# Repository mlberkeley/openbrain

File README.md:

# OpenBrain [[PDF Status](https://www.sharelatex.com/github/repos/mlberkeley/openbrain/builds/latest/badge.svg)](https://www.sharelatex.com/github/repos/mlberkeley/openbrain/builds/latest/output.pdf)
The openBrain project for massive asynchronous neurocomputation. 
Read our [white paper here](https://www.sharelatex.com/github/repos/mlberkeley/openbrain/builds/latest/output.pdf).

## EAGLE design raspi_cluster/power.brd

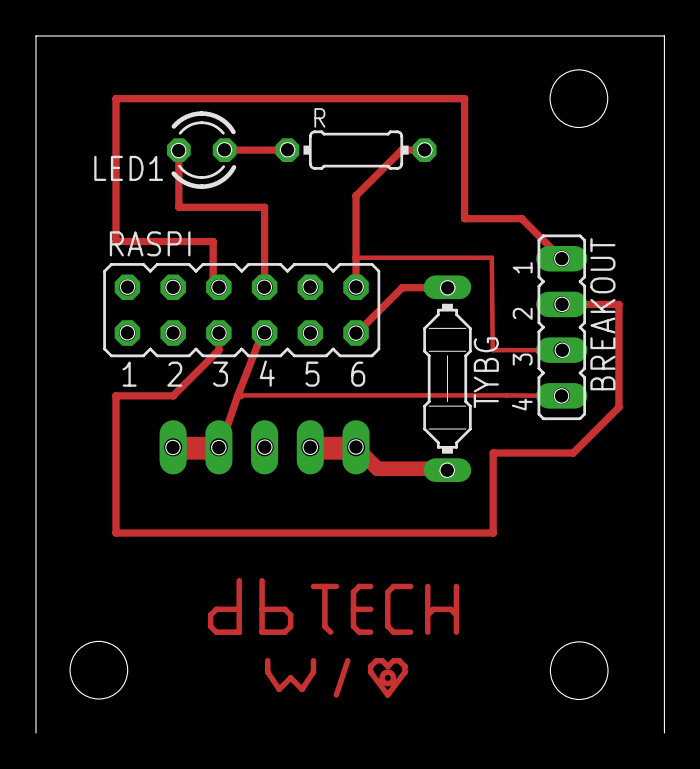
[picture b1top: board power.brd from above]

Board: 2 copper layers, 34.9 x 38.7 mm, 6 parts (1 on the bottom side), 8 nets.

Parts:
5V: 22-23-2051
BREAKOUT: JP4
LED1: TLLR4400; LED3MM
R: 0204/7
RASPI: JP6Q
TYBG: FUSEPICOFUSE; PICOFUSE

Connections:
unnamed: 5V.1, 5V.2, TYBG.2
unnamed: BREAKOUT.3, R.2, RASPI.12
unnamed: LED1.A, R.1
unnamed: BREAKOUT.1, RASPI.6
unnamed: RASPI.11, TYBG.1
unnamed: 5V.4, 5V.5, BREAKOUT.4, RASPI.7
unnamed: BREAKOUT.2, RASPI.5
unnamed: LED1.K, RASPI.8

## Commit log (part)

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2015-12-22 Added a synapto_genesis paper to the research catalogue.
2015-12-22 Added the dentate synaptogenesis paper.
2016-01-03 Working on research proposal.
2016-01-04 Worked on the proposal for plans.
2016-01-04 More work on the proposal
2016-01-04 Working on budget
2016-01-04 Additional work on budget formatting,.
2016-01-04 Finishing budget.
2016-01-04 Finished background
2016-01-04 Misssed something
2016-01-11 Added raspberry pi cluster docs to the repo
2016-01-13 Added schematic and board prototyping for the printed power board
2016-01-13 Proposal finished.
2016-01-13 Moved old panelled schaematic to mirrored and added original, unmirrored version
2016-01-14 adding board_paenl
2016-01-14 the mirror is hereor
2016-01-15 New powerboard break out
2016-01-20 made the printable pcb design
2016-01-20 updated power schematic for breakout board
2016-01-28 The base bracket
2016-02-06 Made copydisk util to facilitate sd card copying
2016-02-08 Removing design directory, minecraft added.
2016-02-09 Some scripts
2016-02-09 Implemented a large portion of the nnerl scheme to emulate what openbrain will be
2016-02-09 this is the time of you lif
2016-02-10 made connections
2016-02-19 Fixed directory of erlang
2016-02-19 penis
2016-02-19 shitballs
2016-02-19 funtimes
2016-02-19 Made code readable, fixed minor bugs with list indexing and confusing names
2016-02-19 Fixed issue with feeding forward, everything should work now. Have yet to test connection
2016-02-20 Fixed issue with feeding forward, everything should work now. Have yet to test connection
    Fix up Jinterface bugs
    Fix java networking issues
    Fix up jinterface
2016-02-20 clean up java package naming
2016-02-20 Moving documents to ML@B|X google drive.
2016-02-20 Removing logs and adding them to git ignore!
2016-02-20 Cleaning up design!
2016-02-22 Fixed up the connection between brain and game
2016-02-24 Renaming raspi_cluster to beowulf since we're constructing a beowulf cluster.
2016-02-24 Deleting eclipse specific files and updating git ignores.
2016-02-27 Adding VPN Erlang connector.
2016-02-27 Adding fantastic Erlang project from ErlIDE
2016-02-27 Working on ERLRIDE and removing Java stuff.
2016-03-04 add more java fun again ;)
2016-03-04 java stuff
2016-03-04 test file adding
2016-03-04 fix my name
2016-03-04 Redid directory structure and moved to IntelliJ from eclipse
2016-03-05 last commit
2016-03-05 Removing .settings files
2016-03-05 Removing emacs from @macsj2005293
2016-03-05 Removing this massive fuckup. git@github.com:mlberkeley/openbrain.git# deleted: javastuff/Stuff/Stuff/Stuff/Stuff/Stuff/Stuff/Stuff/Stuff/.project
2016-03-06 add iml
2016-03-06 Get rid of fluffy robot stuff
2016-03-06 Fixed the function_clause error
2016-03-06 ignore idea stuff
2016-03-06 eliminate idea silliness
2016-03-06 ignore iml
2016-03-06 pregut
2016-03-06 ignore some .idea xml stuff
2016-03-06 add project folder stuff
2016-03-06 remove workspace file
2016-03-06 fix gitignores
2016-03-06 Clean up some more
2016-03-06 Move erlang code into module
2016-03-06 Move everything into one project
2016-03-06 Fix up lib stuff
2016-03-06 Fix up java code more
2016-03-06 get working consistently
2016-03-06 rename LibOpenBrain to brainlib
2016-03-06 Remove duplicate Erlang brain code
2016-03-06 ignore intellij files :sob:
2016-03-06 remove java demo code :broken_heart
2016-03-06 Moved the beowulf folder to its own repo
2016-03-06 remove old mcdemo code
2016-03-06 Cleanup code, comments and todos
2016-03-06 Addding CircleCLI support
2016-03-06 Final post subbranchind development push
2016-04-04 Added whole section on Hutter and Legg's UIM and added a bibliography.
2016-04-04 Added the basic definitions for neural activity.
2016-04-05 Testing mathjaks update
2016-04-05 Finished universal intelligence definitions.
2016-04-06 init commit from jacky!
2016-04-08 added conj 2.4.1
2016-04-08 Added new CTUIM definitions.
2016-04-10 added recoverable environments and convergence conjecture
2016-04-11 Committing old changes
2016-04-14 Added an abstract for the research symposuium.
2016-04-17 I haven't compiled the latex yet -- please do so for me. Updated the core algorithm section.
2016-04-17 no message
2016-04-17 Editing line endings.
2016-04-17 Removing compiled binaries.
2016-04-20 added symposium
2016-04-20 Adding the pacman demo
2016-04-20 shitty boltzmann agent initial implementation
2016-04-20 Finished premptive openbrain agent.
2016-04-20 Cleaning up file.
2016-04-20 added presentation submodule
2016-04-20 added gitignore for pyc. added vectorization of inputs
2016-04-20 modified output to sapmle from all output neurons above threshold
2016-04-20 deleted .pyc
2016-04-20 Cleaning pres1.
2016-04-20 Added new presentation
2016-04-20 Adding to progress presentation.
2016-04-21 added rudimentary learning rule based on refractory periods
2016-04-21 FInished the presentation by adding new Diagrams. CTUIM done!
2016-04-22 Played around with pacman agent and added point-watching into the reinforcement rules.
2016-05-04 wip poster. added abstract, intro, neuron definitions and dynamics, and a gist about uim
2016-08-24 Working on error backpropagation for the framework.
2016-08-24 Defining a simple loss function.
2016-08-25 Fixing the loss function.
2016-08-27 Finished cateogry theory derivation of error backprop.
2016-08-30 Adding CPU support.
2016-08-30 Added a note on synthetic gradients.
2016-09-07 Trying a new conjecture.
2016-09-09 Added the outline for backpropagation free deep reinforcement learning
2016-09-09 Adding new todos formatting.
2016-09-09 Adding a high level description of the section.
2016-09-09 Added the neurocomputational agent definition.
2016-09-09 Defining sub environments.
2016-09-10 Finished definitions for the first conjecture.
2016-09-11 Finished the commutative diagam.
2016-09-12 More paper
2016-09-12 Added the experiment1 specification.
2016-09-12 PDF fix.
2016-09-13 Added DDPG experiment to the repo
2016-09-13 Added new todos for the paper and the new theorem.
2016-09-14 corrected typos, changed some notation to make things clearer, added a bit to "Empirical justification ..." after theorem 2.2.2
2016-09-14 more typo fixes. incomplete
2016-09-14 Added subcritics networks framework. Still have a few todos to reconcile, specifically regarding state and action batches for the subcritic networks.
2016-09-15 Adapted state/action/reward for replay buffer of the subcritic networks.
2016-09-15 Got next_state for each subcritic Fed forward through the actor network to get the state/action values (input/output) of each network
2016-09-15 Add network training for subcritics
2016-09-15 Small change to closer replicate DDPG.train() for the subcritics
    TODO: figure out how to handle target networks for the subcrits
2016-09-15 Fix weird indentation error tabs/spaces are no fun. Python, python come on please run
2016-09-16 Tried fixing q-value batches so that each individual subcritic is assigned its own q-value batch based on layer weight and next_action_batch
2016-09-16 Finished a running version with some bugs Bug fixing right now. Have to deal with issue where action_output has not been evaluated quite yet
2016-09-16 Ubigraph work
2016-09-16 Removing experiment
2016-09-16 Finished the experiment
2016-09-19 Added experimentation section.
2016-09-19 Preliminary experimentation results section.
2016-09-19 added discussion of experiment 1, further explanation of methodology pending.
2016-09-19 Finished preliminary discussion of experiment motivation/methodology. TODO: establish the notion of similiarity to be used in comparing the Q-functions.
2016-09-19 Added notation to Ananth's section
2016-09-19 Reformatted TODO and ready to RUMBLE
2016-09-21 Reorganizing the repository.
2016-09-21 Ignoring all PDFs
2016-09-21 Running travis.
2016-09-21 Fixing the travis script
2016-09-22 Finishing the experimental pull request for travis CI build integration.
2016-09-22 Makinga common directory for the experiments.
2016-09-22 Updating the travis.yml build.
2016-09-22 Cleaning experiment1.py and adding bad logging functions.
2016-09-22 Working DDPG again.
2016-09-22 Fix Link on README
2016-09-22 First draft of intro paragraph on DDPG and DQNs
2016-09-25 Add main statement to experiment1.py
2016-09-25 Polynomial critic
2016-09-25 fixed crashing exp1
2016-09-25 fix exp1 testing
2016-09-29 Added linear case for polynomial critic and annotations. Still need to generalize the case where the polynomial order is greater than 1 so that we can actually use polynomial evaluations. Also need t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
2016-09-30 FInishing tyhe presentation. :)
2016-09-30 Added critic loading and q value function print outs.
2016-10-02 Updated methods to account for polynomial critics.
2016-10-02 Implemented RNN version. Needs to be debugged (does not work very well yet).
2016-10-02 Completed demoday presentation.
2016-10-05 Merge
2016-10-06 add exponential draw for experience replay
2016-10-06 exponential draw from end of buffer
2016-10-06 Add synthetic gradient intro paragraph
2016-10-08 Added tensorboard.
2016-10-08 Creating the graph.
2016-10-08 Finished subcritic construction refactorization.
2016-10-08 Getting the paper to compile.
2016-10-10 Added subcritic training (online w/o batching)
2016-10-10 Finished experiment 1. It works this is awesome.
2016-10-10 Making common experimententation direxctory.
2016-10-10 Cleaning experiment1.
2016-10-10 Fixing directory structure error with experiment.
2016-10-10 Making expweriment 2.
2016-10-13 Added google script for extracting data from tensorboard, didn't work, so fixed it.
2016-10-13 Added bash script for running python script. Usage: ./extractData.sh LOGDIR. Will output data to data/ directory and overwrite anything there.Y
2016-10-13 Added data interface for accessing data from python, only works for the scalar plots, i.e. min, max, stddev, and mean. Will add functions for histograms eventually.
2016-10-13 Added cmd line argument for experiment name, and changed the name of the summary writer directory to this name.
2016-10-13 Added getDistribution function for accessing distribution data, i.e. data from the distributions tab on tensorboard page.
2016-10-13 Fixed extractData.sh
2016-10-22 Added experiment two branch
2016-10-22 Removed subtiming tau and cleaned the background section more.
2016-10-23 Added Layer Class, and Brain Class for experiment two. Not convinced it works but anyway.
2016-10-23 Fixed small bug
2016-10-23 Finished proof of Q gradients being equivalent. Was slightly more complicated than anticipated.
2016-10-23 Added weight logging and removed the last RELU.
2016-10-23 Added exploration noise to each layer
2016-10-24 Added Replay buffer and l2 regularization.
2016-10-24 Minor changes to replay and regularization
2016-10-28 Worked on the experiment with jamesyboy.
2016-10-28 Add new presentation from demoday1 boiler plate
2016-10-28 Working on easy environment
2016-10-28 Add theorems and experiments. Not working.
2016-10-28 Das Osterich ist Autismos
2016-10-28 Working copy of the simple experiment in its current form. :(
2016-10-28 Add more slides and placeholders.
2016-11-11 one neuron
2016-11-11 fix rewardBatch shape
2016-11-14 Adding the experiment3 file
2016-11-17 Add manual logging that saves log values to csvs.
2016-11-20 Remove test code
2016-11-20 add initial correlation analysis code
2016-11-23 ignore exp output
2016-11-23 clean up exp1 analysis commits
2016-11-23 Experiment 3.
2016-11-23 Adding the explorations directory.
2016-11-29 checkin modified prop changes
2016-11-29 compatible policy
2016-11-30 Created Numpy Implementation of Compatible Policy Stuff
2016-12-01 Naive global critix.
2016-12-01 Checking if the numpy implementation is the same as tensorflow
2016-12-02 Add TD error calculations for global critic.
    Basically just replaced Q_value_output with TD.
2016-12-02 Fix up notation.
2016-12-02 Fixing a dumb mistake
2016-12-02 Mountain Car solved with one neuron
2016-12-02 learns in one timestep
2016-12-02 Work on experiment 3 .
2016-12-15 vs work
2016-12-15 Work on two neurons.
2016-12-16 Add rough draft of paper. Need to proof read and fix margins.
